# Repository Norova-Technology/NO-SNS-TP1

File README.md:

# NO-SNS-TP1
Smart environmental sensor
TYPE 1
1. Bluetooth
2. nfc
3. Accelerometer - lis2dh12_LIS2Dx12
4. Temperature sensor - tmp117_TMP117
5. Temp/hum sensor - SHTC3
6. Pressure sensor - DPS310

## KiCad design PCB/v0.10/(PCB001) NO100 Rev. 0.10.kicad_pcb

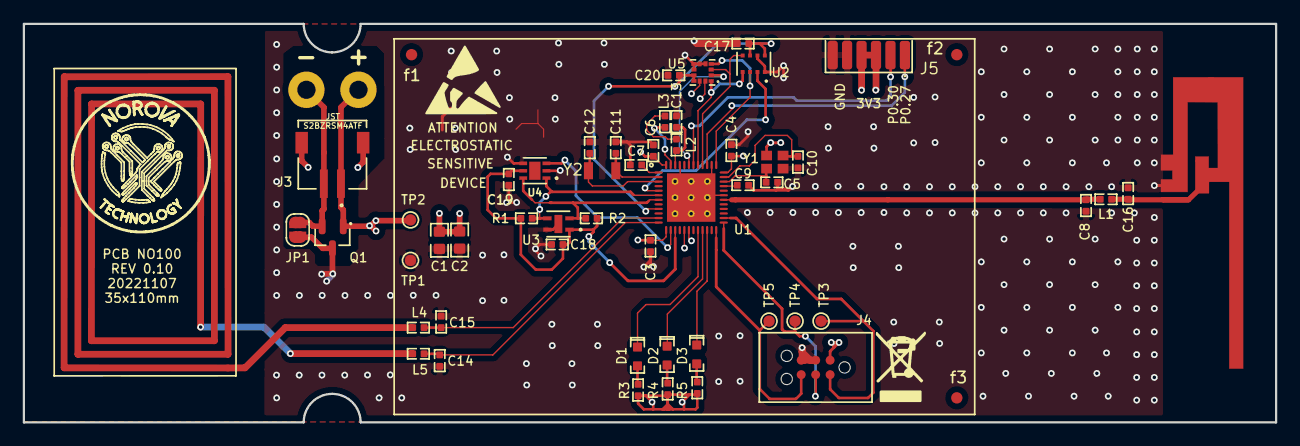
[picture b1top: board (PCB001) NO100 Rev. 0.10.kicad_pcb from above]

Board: 4 copper layers, 110.0 x 35.0 mm, 57 parts (1 on the bottom side), 39 nets.

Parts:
C1, C2: 10uF; SMD_0603_C
C3, C4, C13, C17, C18, C19: 1u; SMD_0402_C
C5, C10, C11, C12: 12p; SMD_0402_C
C6: 4u7; SMD_0402_C
C7: 100n; SMD_0402_C
C8: 0p8; SMD_0402_C
C9: 100p; SMD_0402_C
C14, C15: 130p; SMD_0402_C
C16: 5.6pF; SMD_0402_C
C20: 4.7u; SMD_0402_C
D1, D2, D3: GP_LED; SMD_0603_LED_SML-D12M8WT86
J1: P+; 1pin_1,6_3,2
J2: GND; 1pin_1,6_3,2
J3: S2B-ZR-SM4A-TF(LF)(SN); JST_S2B-ZR-SM4A-TF(LF)(SN)
J4: SWD DEBUG; plugofnails_TC2030-CTX
J5: UART pads; 6_pads_1.27_pitch_BTM
JP1: solder-jp; SolderJumper-2_P1.3mm_Open_RoundedPad1.0x1.5mm
L1: 1.8nH; SMD_0402_L
L2, L3, L4, L5: 15n; SMD_0402_L
P1: NFC_ANT_NOROVA
P2: Inverted_F_ANT_BL_V2
Q1: SI2312BDS-T1-GE3; SOT23-3P96_237X112L42X44
R1, R2, R3, R4, R5: 1k; SMD_0402
TP1, TP2, TP3, TP4, TP5: TestPoint; TestPoint_Pad_D1.0mm
U1: nrf52832_nRF52832; nrf52832
U2: DPS310; XDCR_DPS310
U3: SHTC3-TR-2.5KS; SHTC3
U4: tmp117_TMP117; TMP117MAIDRVT
U5: lis2dh12_LIS2Dx12; LIS2DH12TR
Y1: 4pin_crystal_4PIN_CRYSTAL; 20X16MM_4PIN_CRYSTAL
Y2: 32k; 32X15MM_2PIN_CRYSTAL
f1, f2, f3: Fiducial_1mm_Mask2mm

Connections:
+3V3: C1.1, C2.1, C3.2, C4.2, C6.2, J1.1, J3.1, J4.1, J5.3, J5.4, Q1.1, R3.1, R4.1, R5.1, TP2.1, U1.13, U1.36, U1.48
/MCU Board-controller/ANTENNA: C16.1, L1.2, P2.1
/MCU Board-controller/P0.21_RESET: J4.6, TP5.1, U1.24
/MCU Board-controller/P0.27: J5.1, U1.39
/MCU Board-controller/P0.30: J5.2, U1.42
/MCU Board-controller/SWDCLK: J4.4, TP4.1, U1.25
/MCU Board-controller/SWDIO: J4.2, TP3.1, U1.26
/MCU Board-controller/XC1: C5.2, U1.34, Y1.1
/MCU Board-controller/XC2: C10.2, U1.35, Y1.3
ACC_INT1: U1.17, U5.12
ACC_INT2: U1.18, U5.11
BL_ANT: C8.1, L1.1, U1.30
GND: C1.2, C2.2, C3.1, C4.1, C5.1, C6.1, C7.1, C8.2, C9.1, C10.1, C11.1, C12.1, C13.2, C14.2, C15.1, C16.2, C17.2, C18.2, C19.2, C20.2, J2.1, J3.2, J3.S1, J3.S2, J4.3, J4.5, J5.5, J5.6, JP1.1, JP1.2, P2.2, Q1.2, Q1.3, TP1.1, U1.31, U1.38, U1.45, U1.49, U2.1, U2.7, U3.4, U3.5, U4.2, U4.4, U5.5, U5.6, U5.7, U5.8, Y1.2, Y1.4
LED1: D1.2, U1.20
LED2: D2.2, U1.21
LED3: D3.2, U1.22
MISO: U1.40, U2.5, U5.3
MOSI: U1.37, U2.3, U5.4
NFC1: C15.2, L4.2, U1.11
NFC2: C14.1, L5.1, U1.12
unnamed: C7.2, U1.1
unnamed: C9.2, U1.33
unnamed: C11.2, U1.2, Y2.1
unnamed: C12.2, U1.3, Y2.2
unnamed: C13.1, L2.2, U1.46
unnamed: D1.1, R3.2
unnamed: D2.1, R4.2
unnamed: D3.1, R5.2
unnamed: L2.1, L3.2
unnamed: L3.1, U1.47
unnamed: L5.2, P1.2
SCK: U1.41, U2.4, U5.1
SCL: R2.2, U1.7, U3.2, U4.6
SDA: R1.2, U1.6, U3.3, U4.1
Sensor_power1: C18.1, C19.1, R1.1, R2.1, U1.15, U3.1, U4.5
Sensor_power2: C17.1, C20.1, U1.9, U2.6, U2.8, U5.9, U5.10
~SPI_ACC_CS: U1.43, U5.2
~SPI_PRESS_CS: U1.5, U2.2
~TEMP_ALERT: U1.14, U4.3

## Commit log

2022-07-15 Rename .Enclosure to Enclosure
2022-07-15 Create gitkeep
